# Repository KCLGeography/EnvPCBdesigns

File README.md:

# EnvPCBdesigns
Shield: [![CC BY-NC-SA 4.0][cc-by-nc-sa-shield]][cc-by-nc-sa]

PCB designs for environmental sensors 

This work is licensed under a
[Creative Commons Attribution-NonCommercial-ShareAlike 4.0 International License][cc-by-nc-sa].

**Created by Department of Geography, King's College London, United Kingdom**

[![CC BY-NC-SA 4.0][cc-by-nc-sa-image]][cc-by-nc-sa]

[cc-by-nc-sa]: http://creativecommons.org/licenses/by-nc-sa/4.0/
[cc-by-nc-sa-image]: https://licensebuttons.net/l/by-nc-sa/4.0/88x31.png
[cc-by-nc-sa-shield]: https://img.shields.io/badge/License-CC%20BY--NC--SA%204.0-lightgrey.svg

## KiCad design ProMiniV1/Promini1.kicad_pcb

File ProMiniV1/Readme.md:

# Arduino Pro Mini PCB Design

This folder contains a PCB file for a basic arduino data logger in [kicad](https://www.kicad.org/) format. 

File is available [here](Promini1.kicad_pcb). 

## Bill of Materials
Bill of materials for completed board:
(to be updated)

## Pricing and Ordering
The PCB can be easily ordered through suppliers such as [OSHPark](oshpark.com).

Pricing is approximtely $20 for 3 boards (pricing retrieved 22nd May 2023).

**Created by Dr Bruce Main - Department of Geography, King's College London, United Kingdom**

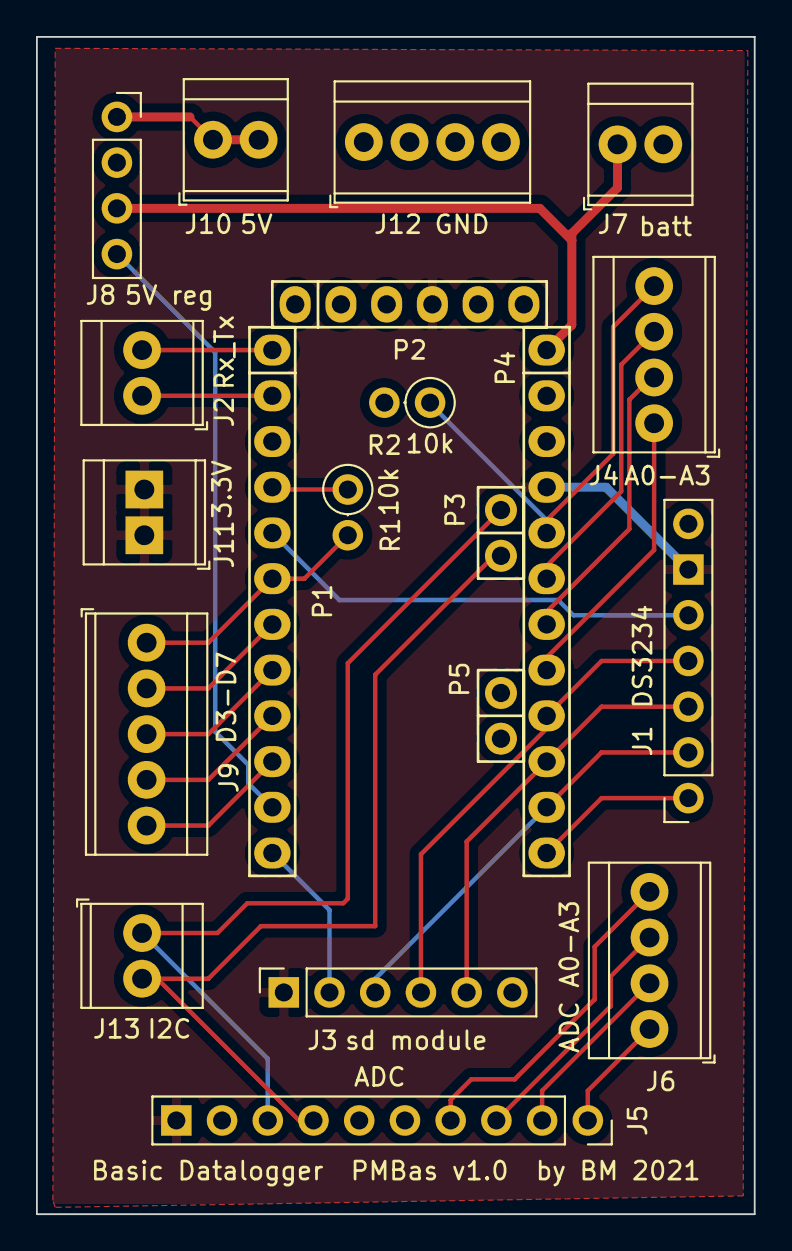
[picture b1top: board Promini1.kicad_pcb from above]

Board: 2 copper layers, 39.9 x 65.4 mm, 20 parts (0 on the bottom side), 28 nets.

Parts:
J1: DS3234; PinSocket_1x07_P2.54mm_Vertical
J2: Rx_Tx; TerminalBlock_TE_282834-2_1x02_P2.54mm_Horizontal
J3: sd module; PinSocket_1x06_P2.54mm_Vertical
J4: A0-A3; TerminalBlock_TE_282834-4_1x04_P2.54mm_Horizontal
J5: ADC; PinSocket_1x10_P2.54mm_Vertical
J6: ADC A0-A3; TerminalBlock_TE_282834-4_1x04_P2.54mm_Horizontal
J7: batt; TerminalBlock_TE_282834-2_1x02_P2.54mm_Horizontal
J8: 5V reg; PinSocket_1x04_P2.54mm_Vertical
J9: D3-D7; TerminalBlock_TE_282834-5_1x05_P2.54mm_Horizontal
J10: 5V; TerminalBlock_TE_282834-2_1x02_P2.54mm_Horizontal
J11: 3.3V; TerminalBlock_TE_282834-2_1x02_P2.54mm_Horizontal
J12: GND; TerminalBlock_TE_282834-4_1x04_P2.54mm_Horizontal
J13: I2C; TerminalBlock_TE_282834-2_1x02_P2.54mm_Horizontal
P1: Digital; Socket_Strip_Arduino_1x12
P2: COM; Socket_Strip_Arduino_1x06
P3: I2C; Socket_Strip_Arduino_1x02
P4: Analog; Socket_Strip_Arduino_1x12
P5: ADC; Socket_Strip_Arduino_1x02
R1, R2: 10k; R_Axial_DIN0207_L6.3mm_D2.5mm_P2.54mm_Vertical

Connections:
GND: J1.7, J3.6, J5.9, J7.2, J8.2, J12.1, J12.2, J12.3, J12.4, P1.4, P2.5, P2.6, P4.2, R1.1, R2.2
unnamed: J1.1, P4.12
unnamed: J1.2, J3.3, P4.11
unnamed: J1.3, J3.5, P4.10
unnamed: J1.4, J3.4, P4.9
unnamed: J1.5, P1.5
unnamed: J2.1, P1.2
unnamed: J2.2, P1.1
unnamed: J3.2, P1.12
unnamed: J4.1, P4.8
unnamed: J4.2, P4.7
unnamed: J4.3, P4.6
unnamed: J4.4, P4.5, R2.1
unnamed: J5.1, J6.1
unnamed: J5.2, J6.2
unnamed: J5.3, J6.3
unnamed: J5.4, J6.4
unnamed: J7.1, J8.3, P4.1
unnamed: J8.4, P1.11
unnamed: J9.1, P1.6, R1.2
unnamed: J9.2, P1.7
unnamed: J9.3, P1.8
unnamed: J9.4, P1.9
unnamed: J9.5, P1.10
unnamed: J8.1, J10.1, J10.2
unnamed: J5.8, J13.1, P3.1
unnamed: J5.7, J13.2, P3.2
VCC: J1.6, J3.1, J5.10, J11.1, J11.2, P2.4, P4.4

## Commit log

2023-05-22 Create LICENCE
2023-05-22 Update LICENCE
